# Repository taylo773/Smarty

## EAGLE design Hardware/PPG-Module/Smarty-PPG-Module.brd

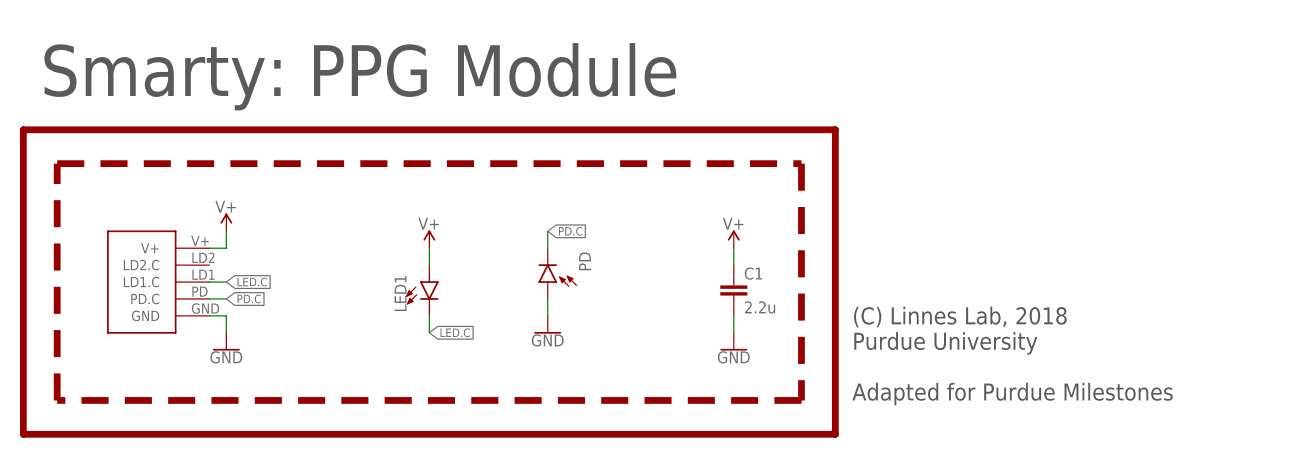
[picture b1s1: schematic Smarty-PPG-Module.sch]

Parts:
C1: 2.2u; C0603
J1: PPG.MODULE.2
LED1: LED0805; LED-0805
PD: PHOTODIODE.-SMD.GULLWING; 2-SMD.GULLWING
U$3: LINNES.LAB.LOGO

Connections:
GND: C1.2, J1.GND, PD.+ (A)
LED.C: J1.LD1 (LD1.C), LED1.C
PD.C: J1.PD (PD.C), PD.- (C)
V+: C1.1, J1.V+, LED1.A

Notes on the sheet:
Smarty: PPG Module
(C) Linnes Lab, 2018 Purdue University Adapted for Purdue Milestones

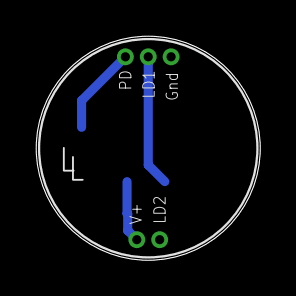
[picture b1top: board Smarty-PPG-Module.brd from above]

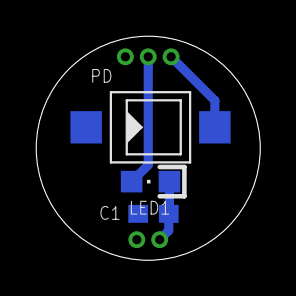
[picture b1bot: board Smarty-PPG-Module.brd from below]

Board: 2 copper layers, 12.4 x 12.4 mm, 5 parts (3 on the bottom side), 4 nets.

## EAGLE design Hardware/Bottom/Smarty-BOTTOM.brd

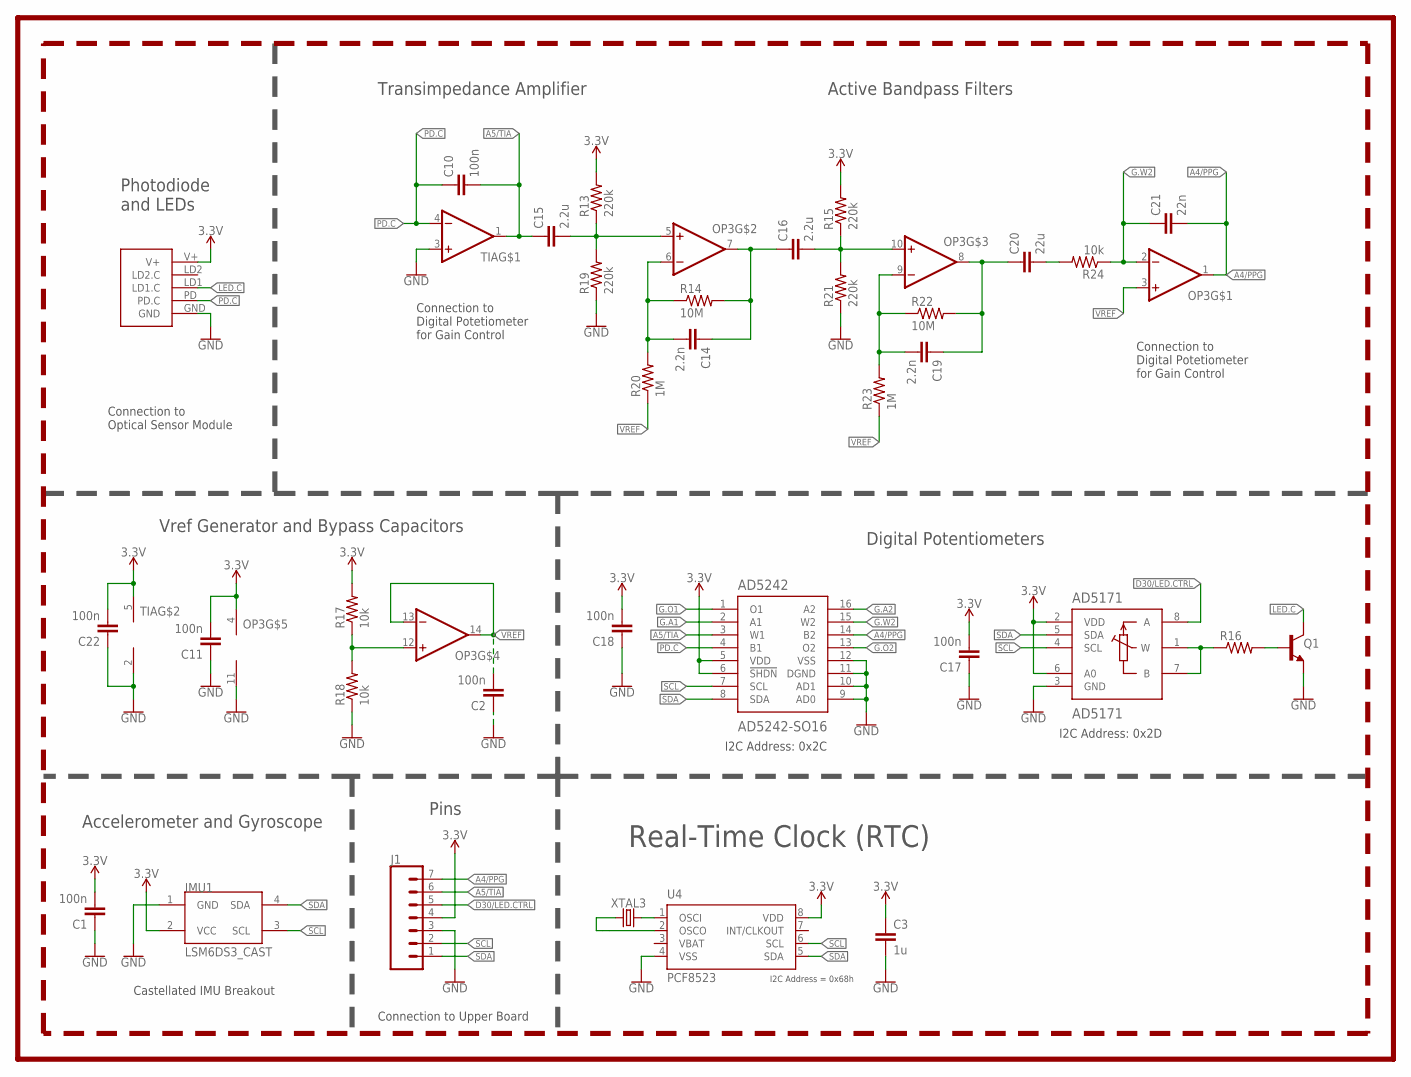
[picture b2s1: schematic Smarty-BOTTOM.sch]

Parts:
AD5171: AD5171; SOT-23-8
AD5242: AD5242-SO16; SO16
C1, C2, C10, C11, C17, C18, C22: 100n; C0603
C3: 1u; C0603
C14, C19: 2.2n; C0603
C15, C16: 2.2u; C0603
C20: 22u; C0603
C21: 22n; C0603
IMU1: LSM6DS3_CAST
J1: CONN_07-1.27MM; 1X07_1.27MM
OP3: OP-QUAD-SO14; SO14
Q1: NPN-GENERIC; SOT23-3
R13, R15, R19, R21: 220k; R0603
R14, R22: 10M; R0603
R16: RESISTOR0603; R0603
R17, R18: 10k; R0402
R20, R23: 1M; R0603
R24: 10k; R0603
TIA: OP-SINGLEOT; SOT23-5
U4: PCF8523; SO8; DIGIKEY 568-5306-1-ND
U$3: PPG.MODULE.2
XTAL3: 32.7680kHz; 2-SMD.NOLEAD.2.0MMTO1.2MM

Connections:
3.3V: AD5171.2 (VDD), AD5171.6 (A0), AD5242.5 (VDD), AD5242.6 (!SHDN), C1.2, C3.1, C11.2, C17.2, C18.2, C22.2, IMU1.2 (VCC), J1.4, OP3.4 (V+), R13.2, R15.2, R17.2, TIA.5 (V+), U4.8 (VDD), U$3.V+
A4/PPG: AD5242.14 (B2), C21.2, J1.7, OP3.1 (OUT)
A5/TIA: AD5242.3 (W1), C10.2, C15.1, J1.6, TIA.1 (OUT)
D30/LED.CTRL: AD5171.8 (A), J1.5
G.A1: AD5242.2 (A1)
G.A2: AD5242.16 (A2)
G.O1: AD5242.1 (O1)
G.O2: AD5242.13 (O2)
G.W2: AD5242.15 (W2), C21.1, OP3.2 (-IN), R24.1
GND: AD5171.3 (GND), AD5242.9 (AD0), AD5242.10 (AD1), AD5242.11 (DGND), AD5242.12 (VSS), C1.1, C2.1, C3.2, C11.1, C17.1, C18.1, C22.1, IMU1.1 (GND), J1.3, OP3.11 (V-), Q1.2 (E), R18.1, R19.1, R21.1, TIA.2 (V-), TIA.3 (+IN), U4.4 (VSS), U$3.GND
LED.C: Q1.3 (C), U$3.LD1 (LD1.C)
unnamed: U4.2 (OSCO), XTAL3.P$1 (1)
unnamed: U4.1 (OSCI), XTAL3.P$2 (2)
unnamed: Q1.1 (B), R16.2
unnamed: AD5171.1 (W), AD5171.7 (B), R16.1
unnamed: OP3.12 (+IN), R17.1, R18.2
unnamed: C15.2, OP3.5 (+IN), R13.1, R19.2
unnamed: C14.2, OP3.6 (-IN), R14.1, R20.2
unnamed: C14.1, C16.1, OP3.7 (OUT), R14.2
unnamed: C16.2, OP3.10 (+IN), R15.1, R21.2
unnamed: C19.2, OP3.9 (-IN), R22.1, R23.2
unnamed: C19.1, C20.1, OP3.8 (OUT), R22.2
unnamed: C20.2, R24.2
PD.C: AD5242.4 (B1), C10.1, TIA.4 (-IN), U$3.PD (PD.C)
SCL: AD5171.4 (SCL), AD5242.7 (SCL), IMU1.3 (SCL), J1.2, U4.6 (SCL)
SDA: AD5171.5 (SDA), AD5242.8 (SDA), IMU1.4 (SDA), J1.1, U4.5 (SDA)
VBAT: U4.3 (VBAT)
VREF: C2.2, OP3.3 (+IN), OP3.13 (-IN), OP3.14 (OUT), R20.1, R23.1

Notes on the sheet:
Photodiode and LEDs
Active Bandpass Filters
Digital Potentiometers
Transimpedance Amplifier
I2C Address: 0x2C
I2C Address: 0x2D
Connection to Optical Sensor Module
Connection to Digital Potetiometer for Gain Control
Connection to Upper Board
Castellated IMU Breakout
Accelerometer and Gyroscope
Pins
Vref Generator and Bypass Capacitors
I2C Address = 0x68h
Real-Time Clock (RTC)

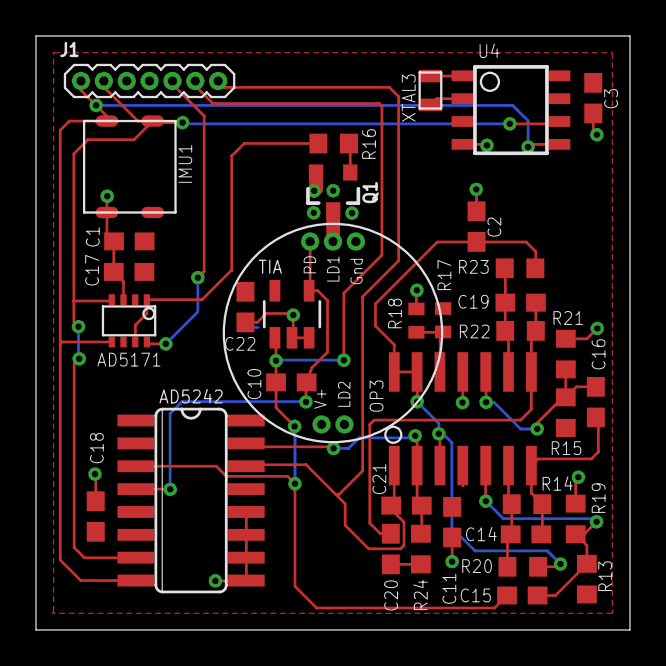
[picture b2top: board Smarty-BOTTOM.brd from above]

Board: 2 copper layers, 33.0 x 33.0 mm, 36 parts (0 on the bottom side), 23 nets.

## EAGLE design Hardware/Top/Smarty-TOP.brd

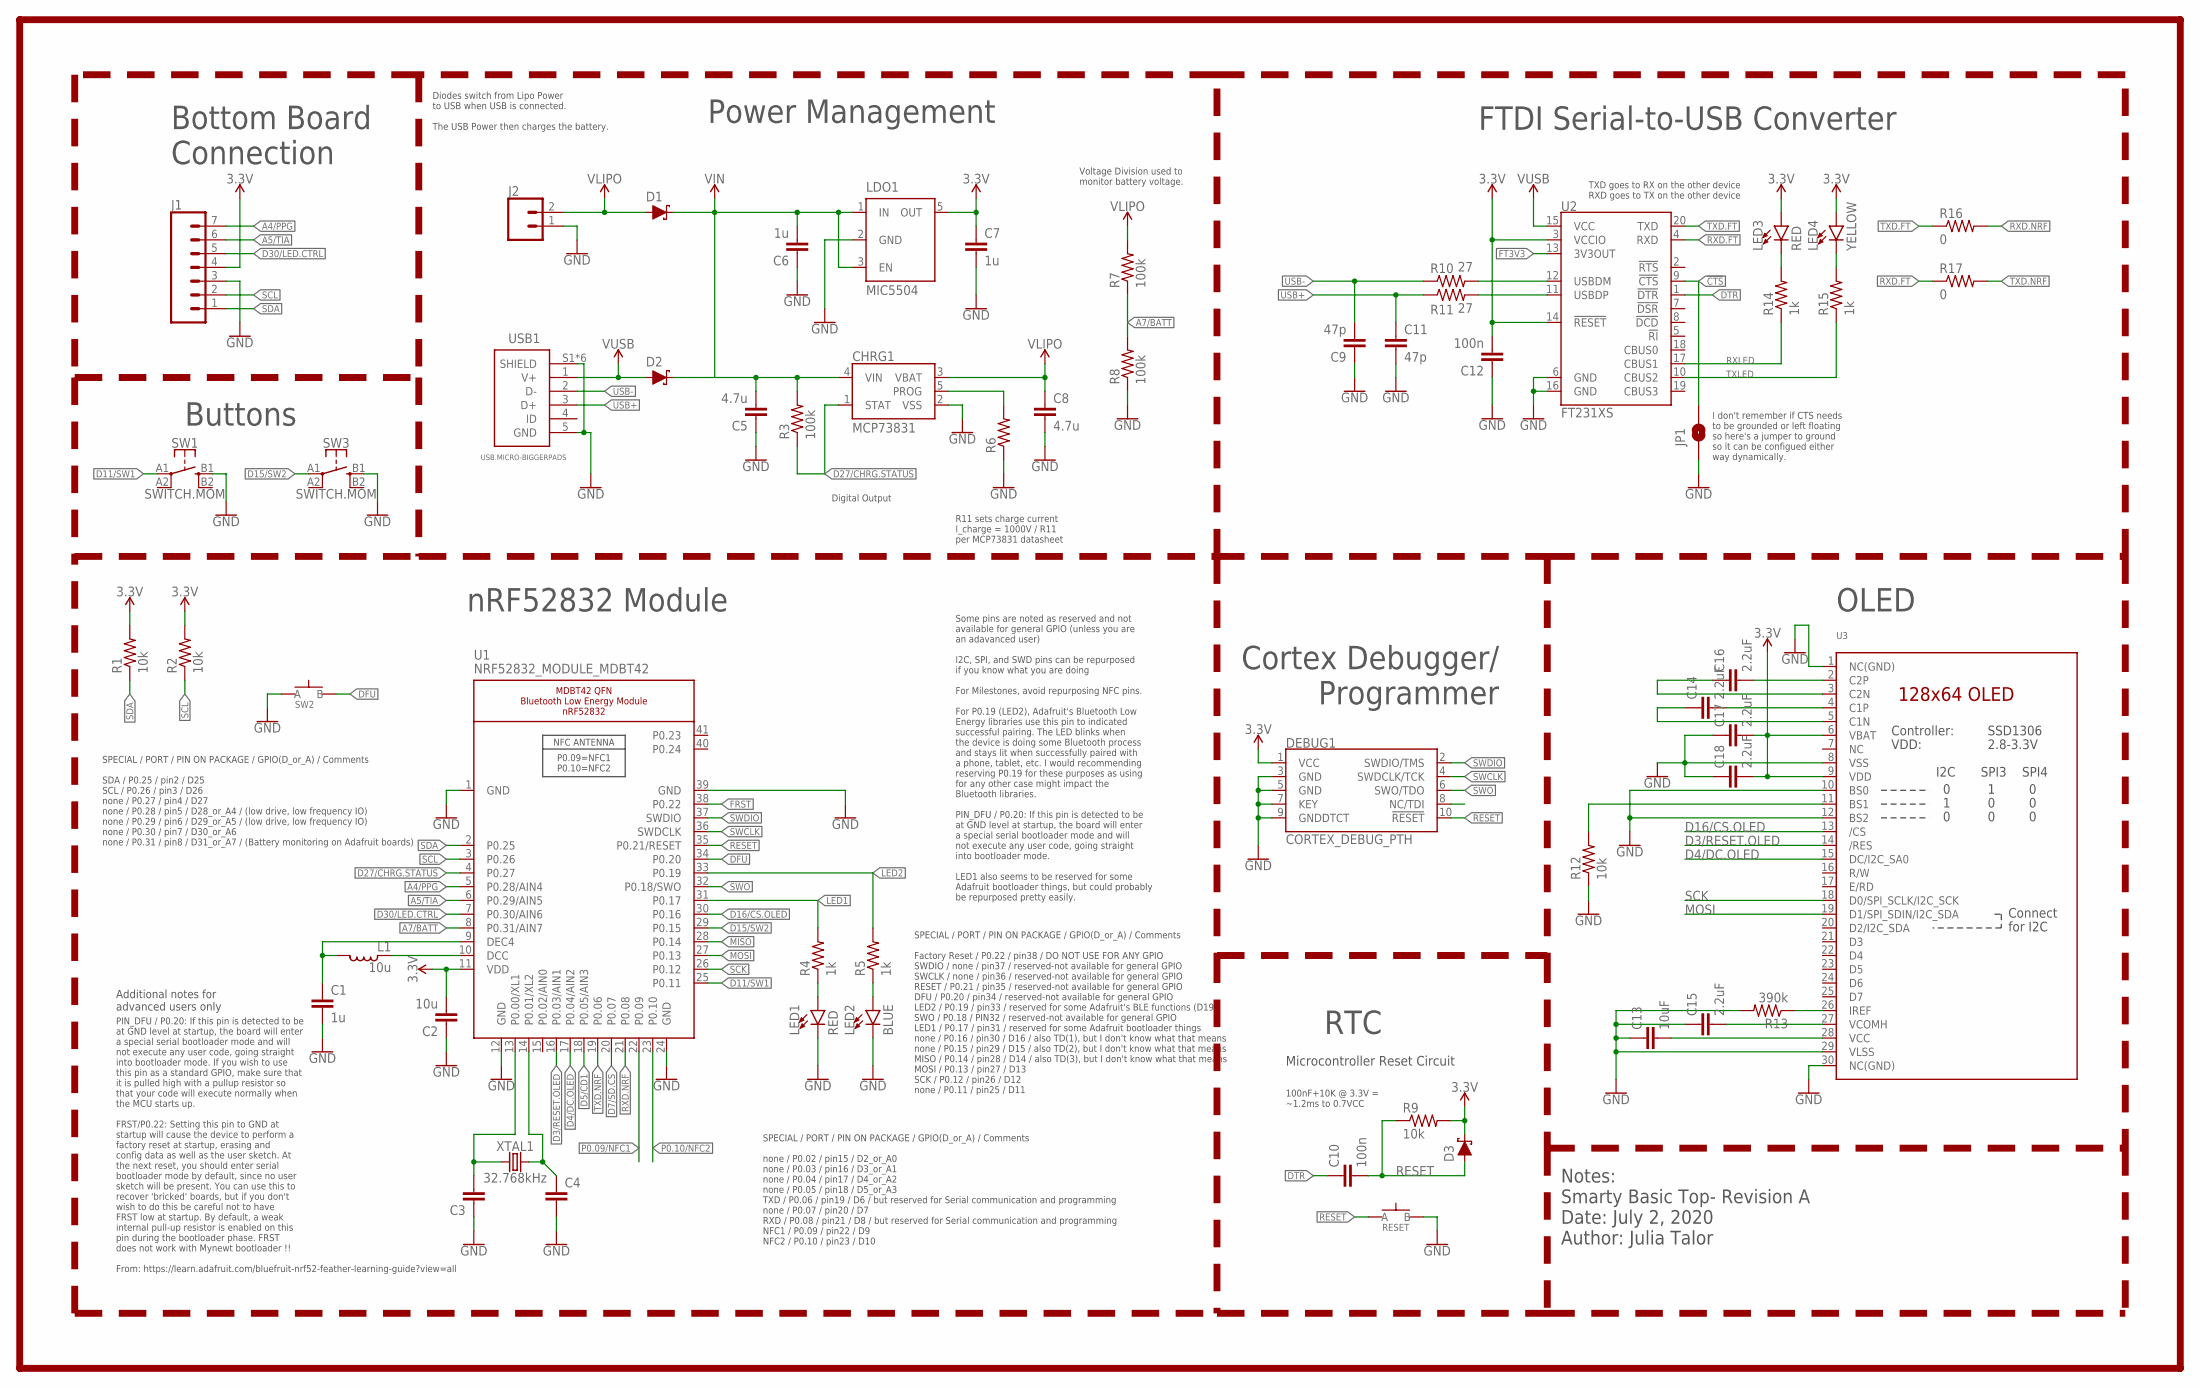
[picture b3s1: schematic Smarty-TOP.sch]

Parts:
C1, C6, C7: 1u; C0603
C2: 10u; C0805
C3, C4: CAPACITOR0603; C0603
C5, C8: 4.7u; C0603
C9, C11: 47p; C0603
C10, C12: 100n; C0603
C13: 10uF; C0603
C14, C16, C17, C18: 2.2uF; C0402
C15: 2.2uF; C0603
CHRG1: MCP73831; SOT23-5
D1, D2, D3: SCHOTTKY-USC; USC
DEBUG1: CORTEX_DEBUG_PTH; 2X5-PTH-1.27MM
J1: CONN_07-1.27MM; 1X07_1.27MM
J2: CONN_02; 1X02
JP1: JUMPER-SMT_2_NO_SILK; SMT-JUMPER_2_NO_SILK
L1: 10u; L0603
LDO1: MIC5504; SOT23-5
LED1, LED3: RED; LED-0603
LED2: BLUE; LED-0603
LED4: YELLOW; LED-0603
R1, R2, R9, R12: 10k; R0603
R3, R7, R8: 100k; R0603
R4, R5, R14, R15: 1k; R0603
R6: RESISTOR0603; R0603
R10, R11: 27; R0603
R13: 390k; R0603
R16, R17: 0; R0603
RESET: SPST-PTS830GG140-COPY.1-3; BUTTON-GULLWING
SW1, SW3: SWITCH.MOM; TACTILE_SWITCH_SMD_6.2MM_TALL
SW2: SPST-PTS830GG140-COPY.1-3; BUTTON-GULLWING
U1: NRF52832_MODULE_MDBT42; BLE_MODULE_RAYTAC_MDBT42
U2: FT231XS; SSOP20_L
U3: DISP_OLED_UG-2864HSWEG01-NO-WRAPAROUND; UG-2864HSWEG01_0.96IN_NO-WRAPAROUND
USB1: USB.MICRO-BIGGERPADS; USB-MICRO-01.BIGGERPADS
XTAL1: 32.768kHz; 2-SMD.NOLEAD.2.0MMTO1.2MM

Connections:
3.3V: C2.2, C7.1, C12.2, C17.2, C18.2, D3.- (C), DEBUG1.1 (VCC), J1.4, LDO1.5 (OUT), LED3.A, LED4.A, R1.2, R2.2, R9.2, U1.11 (VDD), U2.3 (VCCIO), U2.14 (!RESET), U3.6 (VBAT), U3.9 (VDD)
!CTS: JP1.2, U2.9 (!CTS)
A4/PPG: J1.7, U1.5 (P0.28/AIN4)
A5/TIA: J1.6, U1.6 (P0.29/AIN5)
A7/BATT: R7.1, R8.2, U1.8 (P0.31/AIN7)
D3/RESET.OLED: U1.16 (P0.03/AIN1), U3.14 (/RES)
D4/DC.OLED: U1.17 (P0.04/AIN2), U3.15 (DC/I2C_SA0)
D5/CD1: U1.18 (P0.05/AIN3)
D7/SD.CS: U1.20 (P0.07)
D11/SW1: SW1.A1 (1), U1.25 (P0.11)
D15/SW2: SW3.A1 (1), U1.29 (P0.15)
D16/CS.OLED: U1.30 (P0.16), U3.13 (/CS)
D27/CHRG.STATUS: CHRG1.1 (STAT), R3.1, U1.4 (P0.27)
D30/LED.CTRL: J1.5, U1.7 (P0.30/AIN6)
DFU: SW2.3 (B), U1.34 (P0.20)
DTR: C10.1, U2.1 (!DTR)
FRST: U1.38 (P0.22)
FT3V3: U2.13 (3V3OUT)
GND: C1.2, C2.1, C3.1, C4.2, C5.1, C6.1, C7.2, C8.2, C9.1, C11.2, C12.1, C13.1, C15.1, C17.1, C18.1, CHRG1.2 (VSS), DEBUG1.3 (GND), DEBUG1.5 (GND), DEBUG1.7 (KEY), DEBUG1.9 (GNDDTCT), J1.3, J2.1, JP1.1, LDO1.2 (GND), LED1.C, LED2.C, R6.1, R8.1, R12.1, R13.2, RESET.3 (B), SW1.B1 (3), SW2.1 (A), SW3.B1 (3), U1.1 (GND), U1.12 (GND), U1.24 (GND), U1.39 (GND), U2.6 (GND), U2.16 (GND), U3.1 (NC(GND)), U3.8 (VSS), U3.10 (BS0), U3.12 (BS2), U3.29 (VLSS), U3.30 (NC(GND)), USB1.5 (GND), USB1.S1 (SHIELD), USB1.S2 (SHIELD), USB1.S3 (SHIELD), USB1.S4 (SHIELD), USB1.S5 (SHIELD), USB1.S6 (SHIELD)
LED1: R4.2, U1.31 (P0.17)
LED2: R5.2, U1.33 (P0.19)
MISO: U1.28 (P0.14)
MOSI: U1.27 (P0.13), U3.19 (D1/SPI_SDIN/I2C_SDA)
unnamed: R12.2, U3.11 (BS1)
unnamed: R13.1, U3.26 (IREF)
unnamed: C16.2, U3.2 (C2P)
unnamed: CHRG1.5 (PROG), R6.2
unnamed: C16.1, U3.3 (C2N)
unnamed: C14.2, U3.4 (C1P)
unnamed: C14.1, U3.5 (C1N)
unnamed: R10.2, U2.12 (USBDM)
unnamed: R11.2, U2.11 (USBDP)
unnamed: C13.2, U3.28 (VCC)
unnamed: LED3.C, R14.2
unnamed: C15.2, U3.27 (VCOMH)
unnamed: LED4.C, R15.2
unnamed: C3.2, U1.13 (P0.00/XL1), XTAL1.P$1 (1)
unnamed: C4.1, U1.14 (P0.01/XL2), XTAL1.P$2 (2)
unnamed: LED1.A, R4.1
unnamed: LED2.A, R5.1
unnamed: L1.1, U1.10 (DCC)
unnamed: C1.1, L1.2, U1.9 (DEC4)
P0.09/NFC1: U1.22 (P0.09)
P0.10/NFC2: U1.23 (P0.10)
RESET: C10.2, D3.+ (A), DEBUG1.10 (!RESET), R9.1, RESET.1 (A), U1.35 (P0.21/RESET)
RXD.FT: R17.1, U2.4 (RXD)
RXD.NRF: R16.2, U1.21 (P0.08)
RXLED: R14.1, U2.17 (CBUS1)
SCK: U1.26 (P0.12), U3.18 (D0/SPI_SCLK/I2C_SCK)
SCL: J1.2, R2.1, U1.3 (P0.26)
SDA: J1.1, R1.1, U1.2 (P0.25)
SWCLK: DEBUG1.4 (SWDCLK/TCK), U1.36 (SWDCLK)
SWDIO: DEBUG1.2 (SWDIO/TMS), U1.37 (SWDIO)
SWO: DEBUG1.6 (SWO/TDO), U1.32 (P0.18/SWO)
TXD.FT: R16.1, U2.20 (TXD)
TXD.NRF: R17.2, U1.19 (P0.06)
TXLED: R15.1, U2.10 (CBUS2)
USB+: C11.1, R11.1, USB1.3 (D+)
USB-: C9.2, R10.1, USB1.2 (D-)
VIN: C5.2, C6.2, CHRG1.4 (VIN), D1.- (C), D2.- (C), LDO1.1 (IN), LDO1.3 (EN), R3.2
VLIPO: C8.1, CHRG1.3 (VBAT), D1.+ (A), J2.2, R7.2
V_USB: D2.+ (A), U2.15 (VCC), USB1.1 (V+)

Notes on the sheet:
OLED
Cortex Debugger/ Programmer
nRF52832 Module
Power Management
Buttons
RTC
Microcontroller Reset Circuit
100nF+10K @ 3.3V = ~1.2ms to 0.7VCC
SPECIAL / PORT / PIN ON PACKAGE / GPIO(D_or_A) / Comments SDA / P0.25 / pin2 / D25 SCL / P0.26 / pin3 / D26 none / P0.27 / pin4 / D27 none / P0.28 / pin5 / D28_or_A4 / (low drive, low frequency IO) none / P0.29 / pin6 / D29_or_A5 / (low drive, low frequency IO) none / P0.30 / pin7 / D30_or_A6 none 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
SPECIAL / PORT / PIN ON PACKAGE / GPIO(D_or_A) / Comments none / P0.02 / pin15 / D2_or_A0 none / P0.03 / pin16 / D3_or_A1 none / P0.04 / pin17 / D4_or_A2 none / P0.05 / pin18 / D5_or_A3 TXD / P0.06 / pin19 / D6 / but reserved for Serial communication and programming none / P0.07 / pin20 / D7 RXD / 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
SPECIAL / PORT / PIN ON PACKAGE / GPIO(D_or_A) / Comments Factory Reset / P0.22 / pin38 / DO NOT USE FOR ANY GPIO SWDIO / none / pin37 / reserved-not available for general GPIO SWCLK / none / pin36 / reserved-not available for general GPIO RESET / P0.21 / pin35 / reserved-not available for general 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
Some pins are noted as reserved and not available for general GPIO (unless you are an adavanced user) I2C, SPI, and SWD pins can be repurposed if you know what you are doing For Milestones, avoid repurposing NFC pins. For P0.19 (LED2), Adafruit's Bluetooth Low Energy libraries use this pin to indic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
PIN_DFU / P0.20: If this pin is detected to be at GND level at startup, the board will enter a special serial bootloader mode and will not execute any user code, going straight into bootloader mode. If you wish to use this pin as a standard GPIO, make sure that it is pulled high with a pullup resis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
Additional notes for advanced users only
TXD goes to RX on the other device RXD goes to TX on the other device
I don't remember if CTS needs to be grounded or left floating so here's a jumper to ground so it can be configued either way dynamically.
FTDI Serial-to-USB Converter
Digital Output
Bottom Board Connection
Notes: Smarty Basic Top- Revision A Date: July 2, 2020 Author: Julia Talor
Diodes switch from Lipo Power to USB when USB is connected. The USB Power then charges the battery.
R11 sets charge current I_charge = 1000V / R11 per MCP73831 datasheet
Voltage Division used to monitor battery voltage.

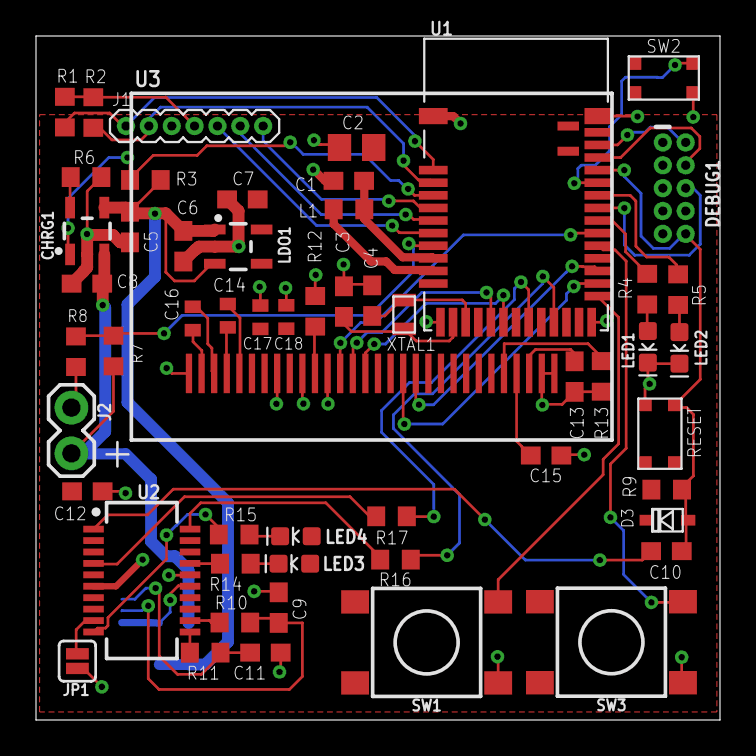
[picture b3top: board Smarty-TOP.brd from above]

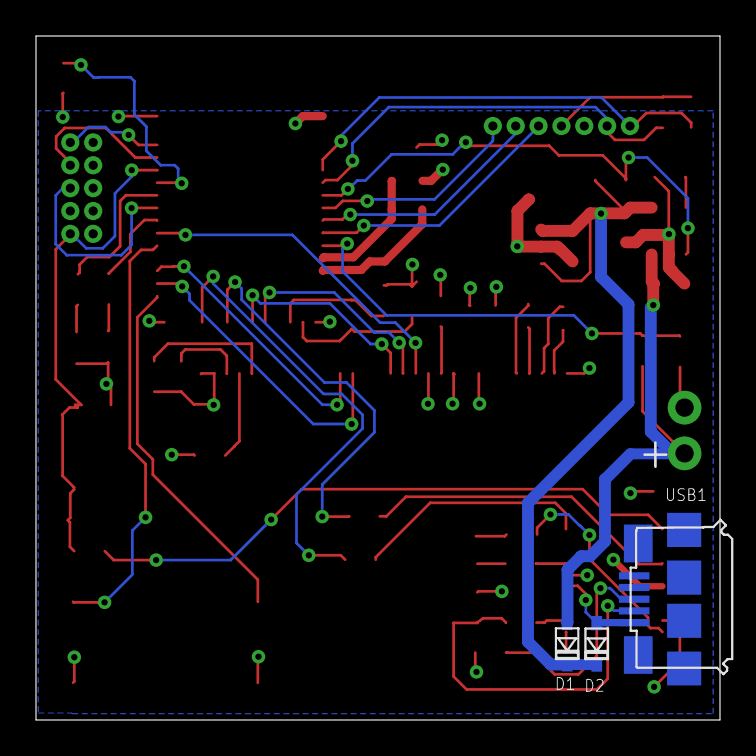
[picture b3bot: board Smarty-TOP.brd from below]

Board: 2 copper layers, 38.0 x 38.0 mm, 58 parts (3 on the bottom side), 55 nets.

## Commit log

2020-05-28 Name and Features of Smarty
2020-05-28 Name and Features of Smarty 05-28-20
2020-06-04 Features List
2020-06-04 .gitignore file
2020-06-04 Firmware Folder
2020-06-04 Hardware Folder
2020-06-05 Edits on 06-04-20 TOP Boards and Schematics
2020-06-11 Take 001 and part of Take 002 Completed
2020-06-11 Rm b1
2020-06-11 Rm b2
2020-06-11 Rm b3
2020-06-11 Rm s1
2020-06-11 Rm s2
2020-06-11 Rm s3
2020-06-11 Finished Take 2
2020-06-25 Object Oriented Programming Video
2020-06-25 Finished Take 004, Airwire Errors
2020-06-25 Finished Take 004
2020-06-25 Finished Take 005, Airwire Errors
2020-06-26 Finished Take 006
2020-07-02 Almost dont with Take 008
2020-07-02 Almost Done With Take 008
2020-07-02 Finished Take 008
2020-07-02 Beginning Files
2020-07-03 29:44 Mark Take 1 Programming
2020-07-08 Take 001 Programming 1:09
2020-07-08 Remove file
2020-07-08 Take 001 1:09:02
2020-07-09 Remove Files to Replace
2020-07-09 Remove Files
2020-07-09 Finished BOM Video
2020-07-09 PPG Files
2020-07-09 Consolidated Files
